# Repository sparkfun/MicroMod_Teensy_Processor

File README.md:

SparkFun MicroMod Teensy Processor Board 
========================================

[SparkFun MicroMod Teensy Processor Board](https://www.sparkfun.com/products/16402)

The SparkFun MicroMod Teensy Processor Board leverages the incredible computing power of the NXP iMXRT1062 chip and pairs it with the M.2 MicroMod connector to allow you to plug it into your choice of compatible SparkFun MicroMod Carrier Board.

Repository Contents
-------------------

* **/Documents** - Datasheets, schematic, etc.
* **/Hardware** - Eagle design files (.brd, .sch)

Documentation
--------------
* **[Hookup Guide](https://learn.sparkfun.com/tutorials/micromod-teensy-processor-hookup-guide)** - Basic hookup guide for the SparkFun MicroMod Teensy Processor Board
* **[MicroMod Info Page](https://www.sparkfun.com/micromod)** - MicroMod Information Page

Version History
---------------
* **[DEV-16402](https://www.sparkfun.com/products/16402)** - Initial release.

License Information
-------------------

This product is _**open source**_! 

Please review the LICENSE.md file for license information. 

If you have any questions or concerns on licensing, please contact technical support on our [SparkFun forums](https://forum.sparkfun.com/viewforum.php?f=152).

Distributed as-is; no warranty is given.

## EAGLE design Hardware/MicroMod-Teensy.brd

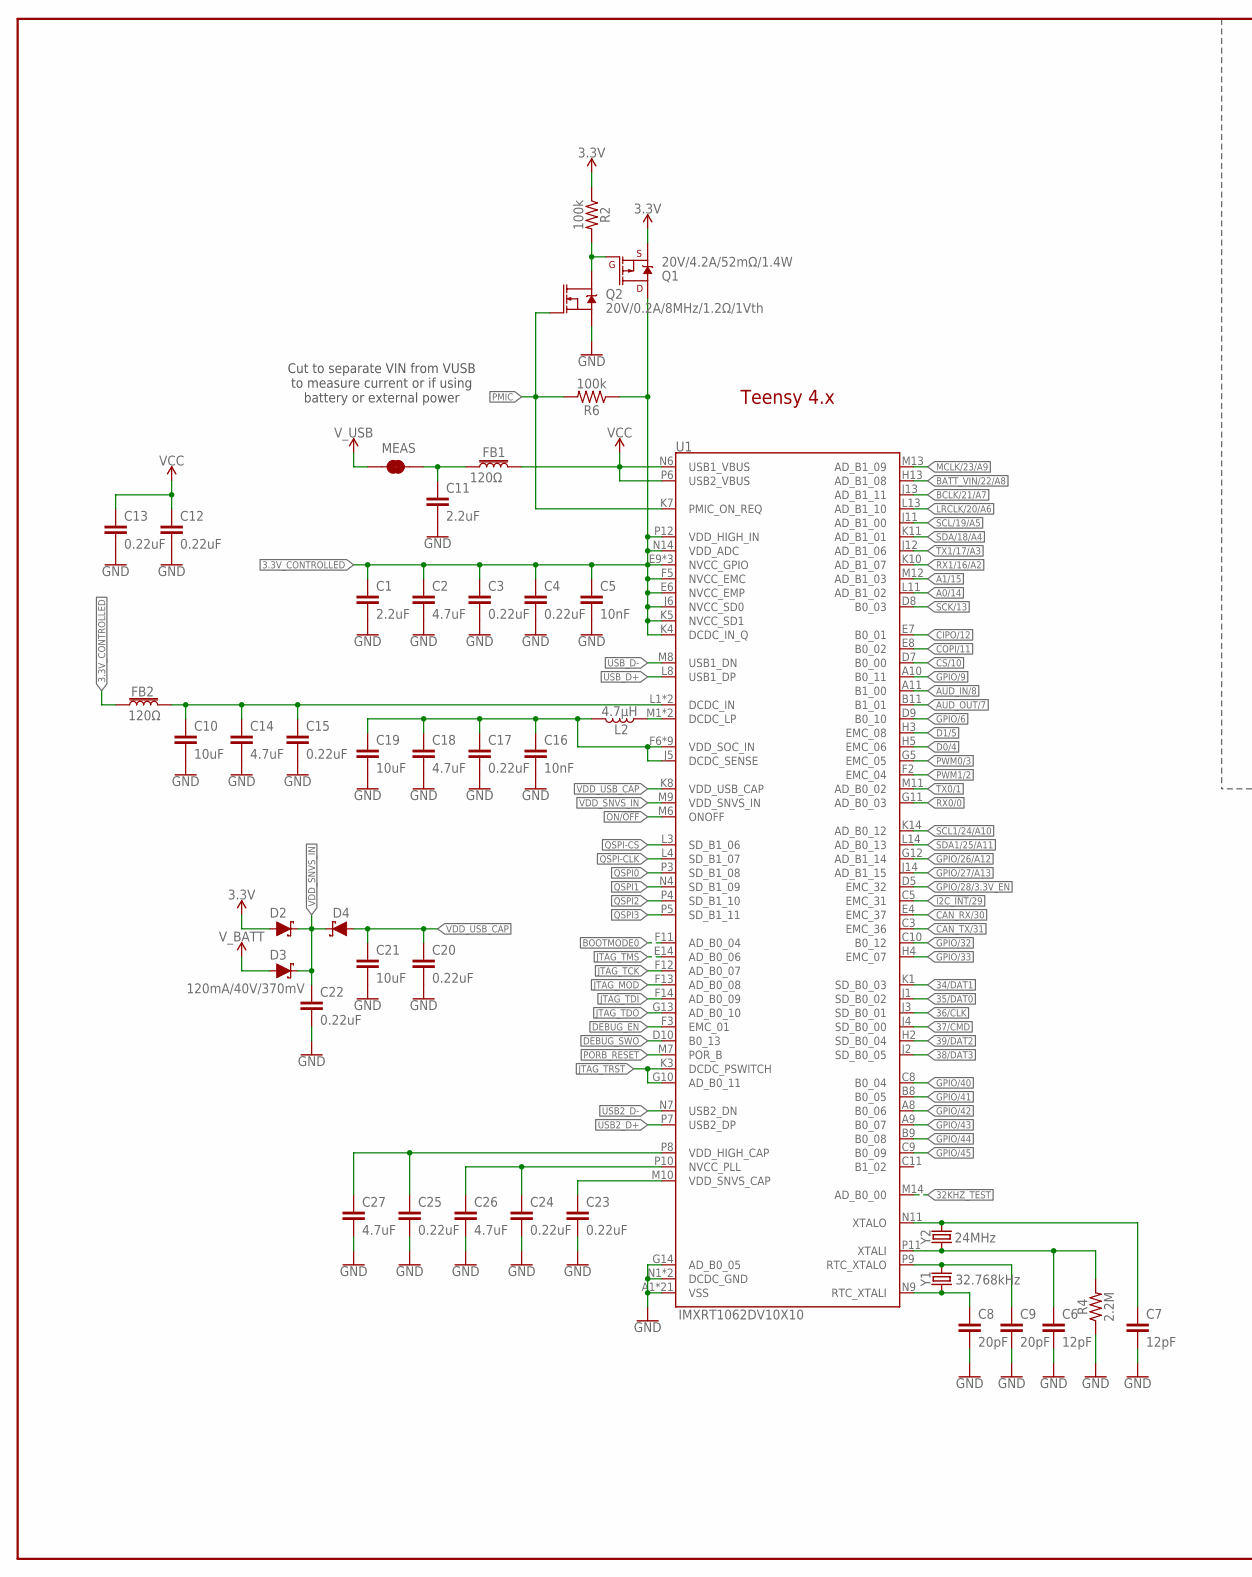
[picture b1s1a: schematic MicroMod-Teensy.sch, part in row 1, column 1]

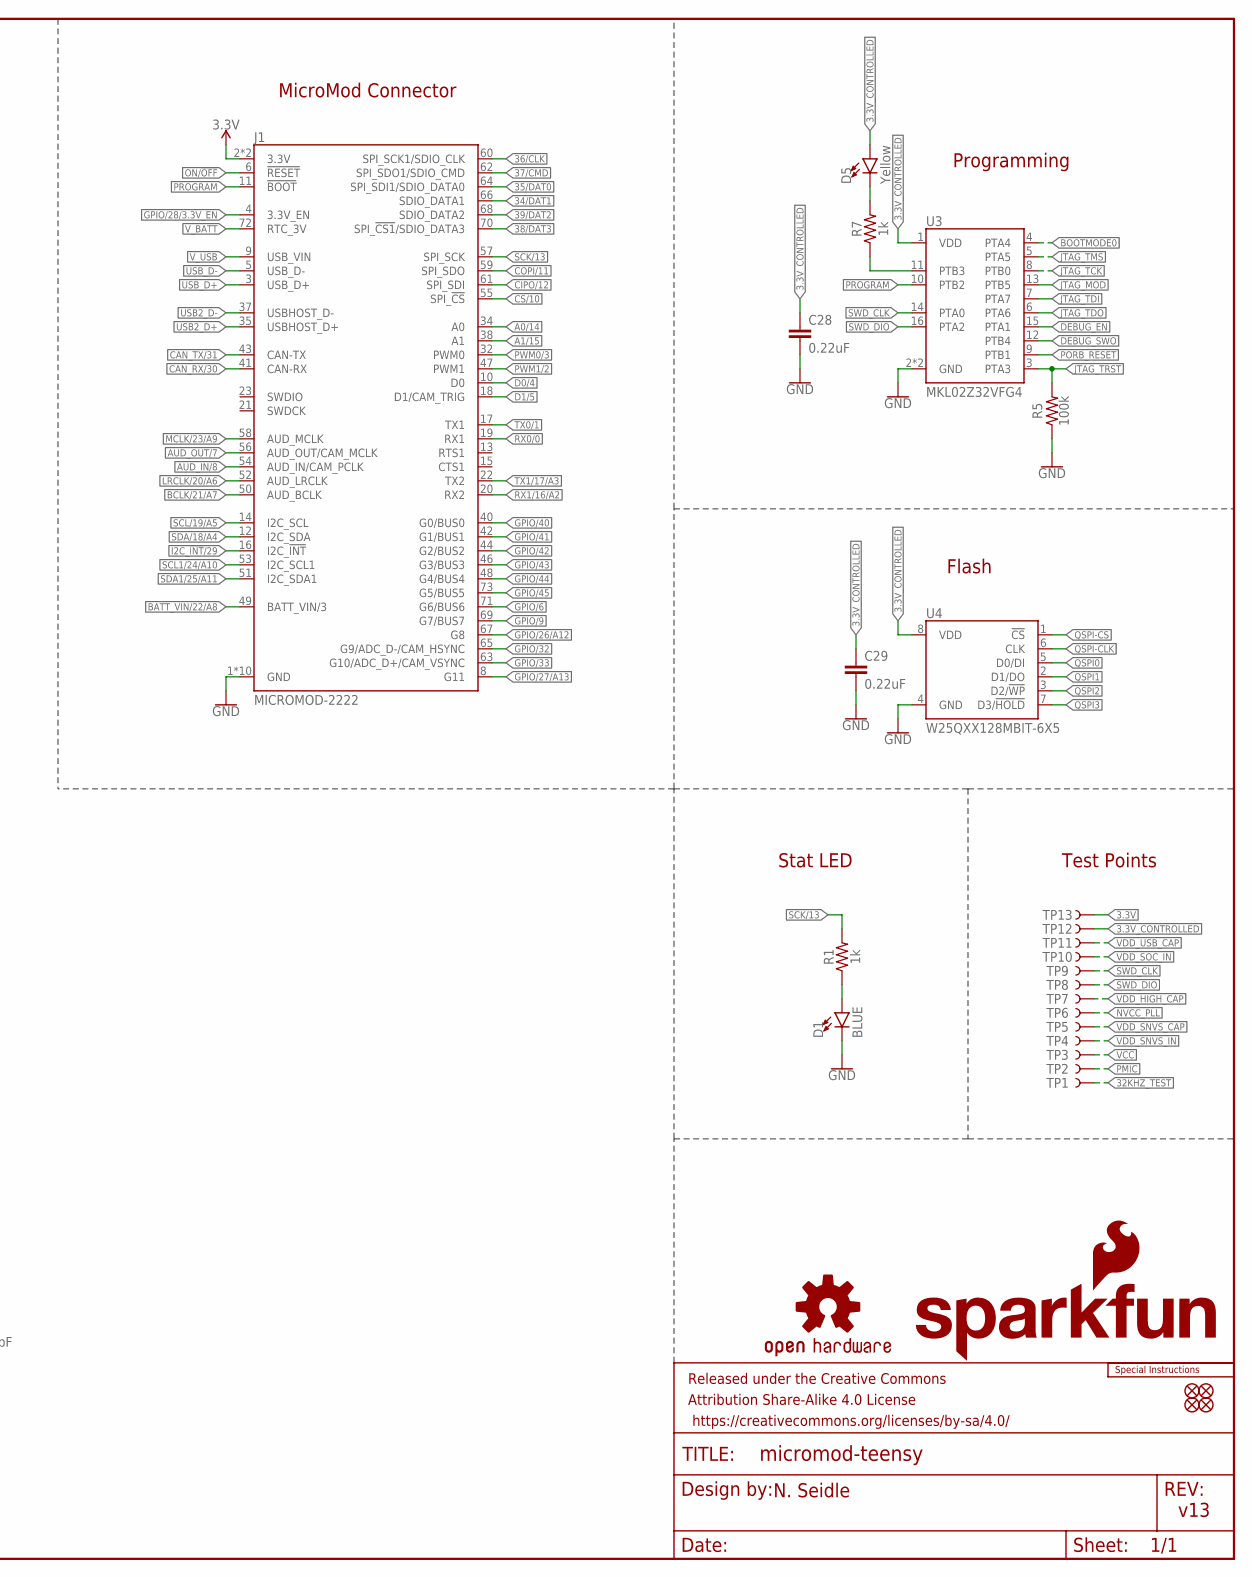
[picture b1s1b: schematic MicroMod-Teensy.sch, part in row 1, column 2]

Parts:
C1, C11: 2.2uF; 0402-TIGHT
C2, C14, C18, C26, C27: 4.7uF; 0402-TIGHT
C3, C4, C12, C13, C15, C17, C20, C22, C23, C24, C25, C28, C29: 0.22uF; 0402-TIGHT
C5, C16: 10nF; 0402-TIGHT
C6, C7: 12pF; 0402-TIGHT
C8, C9: 20pF; 0402-TIGHT
C10, C19, C21: 10uF; 0402-TIGHT
D1: BLUE; LED-0603
D2, D3, D4: 120mA/40V/370mV; SOD-523
D5: Yellow; LED-0603
FB1, FB2: 120Ω; 0402-TIGHT
FD1, FD2, FD3, FD4: FIDUCIALUFIDUCIAL; FIDUCIAL-MICRO
FRAME1: FRAME-LEDGER; CREATIVE_COMMONS
J1: MICROMOD-2222; M.2-CARD-E-22
L2: 4.7μH; 1008(2520)
LOGO1: SFE_LOGO_NAME_FLAME.1_INCH; SFE_LOGO_NAME_FLAME_.1
LOGO2: OSHW-LOGONO_SILK; DUMMY
LOGO3: SPECIAL_INSTRUCTIONS-ORDERING; ORDERING_INSTRUCTIONS
MEAS: JUMPER-SMT_2_NC_TRACE_SILK; SMT-JUMPER_2_NC_TRACE_SILK
Q1: 20V/4.2A/52mΩ/1.4W; SOT23-3
Q2: 20V/0.2A/8MHz/1.2Ω/1Vth; SOT-416FL
R1, R7: 1k; 0402-TIGHT
R2, R5, R6: 100k; 0402-TIGHT
R4: 2.2M; 0402-TIGHT
TP1, TP2, TP3, TP4, TP5, TP6, TP7, TP8, TP9, TP10, TP11, TP12, TP13: TEST-POINT3; PAD.03X.03
U1: IMXRT1062DV10X10; IMXRT1062
U3: MKL02Z32VFG4; QFN-16
U4: W25QXX128MBIT-6X5; WSON-8-6X5-SKINNY_CENTERPAD
Y1: 32.768kHz; CRYSTAL-SMD-3.2X1.5MM
Y2: 24MHz; CRYSTAL-SMD-2.0X1.6MM

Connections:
3.3V: D2.A, J1.2 (3.3V), J1.74 (3.3V), Q1.2 (S), R2.1, TP13.P$1
3.3V_CONTROLLED: C1.1, C2.1, C3.1, C4.1, C5.1, C28.1, C29.1, D5.A, FB2.1, Q1.3 (D), R6.1, TP12.P$1, U1.E6 (NVCC_EMP), U1.E9 (NVCC_GPIO), U1.F5 (NVCC_EMC), U1.F10 (NVCC_GPIO), U1.J6 (NVCC_SD0), U1.J10 (NVCC_GPIO), U1.K4 (DCDC_IN_Q), U1.K5 (NVCC_SD1), U1.N14 (VDD_ADC), U1.P12 (VDD_HIGH_IN), U3.1 (VDD), U4.8 (VDD)
24MHZ_1: C7.1, U1.N11 (XTALO), Y2.3 (2)
24MHZ_2: C6.1, R4.2, U1.P11 (XTALI), Y2.1
32KHZ_1: C8.1, U1.N9 (RTC_XTALI), Y1.P$1 (1)
32KHZ_2: C9.1, U1.P9 (RTC_XTALO), Y1.P$2 (2)
32KHZ_TEST: TP1.P$1, U1.M14 (AD_B0_00)
34/DAT1: J1.66 (SDIO_DATA1), U1.K1 (SD_B0_03)
35/DAT0: J1.64 (SPI_SDI1/SDIO_DATA0), U1.J1 (SD_B0_02)
36/CLK: J1.60 (SPI_SCK1/SDIO_CLK), U1.J3 (SD_B0_01)
37/CMD: J1.62 (SPI_SDO1/SDIO_CMD), U1.J4 (SD_B0_00)
38/DAT3: J1.70 (SPI_!CS1!/SDIO_DATA3), U1.J2 (SD_B0_05)
39/DAT2: J1.68 (SDIO_DATA2), U1.H2 (SD_B0_04)
A0/14: J1.34 (A0), U1.L11 (AD_B1_02)
A1/15: J1.38 (A1), U1.M12 (AD_B1_03)
AUD_IN/8: J1.54 (AUD_IN/CAM_PCLK), U1.A11 (B1_00)
AUD_OUT/7: J1.56 (AUD_OUT/CAM_MCLK), U1.B11 (B1_01)
BATT_VIN/22/A8: J1.49 (BATT_VIN/3), U1.H13 (AD_B1_08)
BCLK/21/A7: J1.50 (AUD_BCLK), U1.J13 (AD_B1_11)
BOOTMODE0: U1.F11 (AD_B0_04), U3.4 (PTA4)
CAN_RX/30: J1.41 (CAN-RX), U1.E4 (EMC_37)
CAN_TX/31: J1.43 (CAN-TX), U1.C3 (EMC_36)
CIPO/12: J1.61 (SPI_SDI), U1.E7 (B0_01)
COPI/11: J1.59 (SPI_SDO), U1.E8 (B0_02)
CS/10: J1.55 (SPI_!CS!), U1.D7 (B0_00)
D0/4: J1.10 (D0), U1.H5 (EMC_06)
D1/5: J1.18 (D1/CAM_TRIG), U1.H3 (EMC_08)
DCDC_IN: C10.1, C14.1, C15.1, FB2.2, U1.L1 (DCDC_IN), U1.L2 (DCDC_IN)
DCDC_LP: L2.1, U1.M1 (DCDC_LP), U1.M2 (DCDC_LP)
DEBUG_EN: U1.F3 (EMC_01), U3.15 (PTA1)
DEBUG_SWO: U1.D10 (B0_13), U3.12 (PTB4)
GND: C1.2, C2.2, C3.2, C4.2, C5.2, C6.2, C7.2, C8.2, C9.2, C10.2, C11.2, C12.2, C13.2, C14.2, C15.2, C16.2, C17.2, C18.2, C19.2, C20.2, C21.2, C22.2, C23.2, C24.2, C25.2, C26.2, C27.2, C28.2, C29.2, D1.C, J1.1 (GND), J1.7 (GND), J1.33 (GND), J1.36 (GND), J1.39 (GND), J1.45 (GND), J1.75 (GND), J1.GND1 (GND), J1.GND2 (GND), J1.GND3 (GND), Q2.2 (S), R4.1, R5.1, U1.A1 (VSS), U1.A14 (VSS), U1.B5 (VSS), U1.B10 (VSS), U1.E2 (VSS), U1.E13 (VSS), U1.G7 (VSS), U1.G8 (VSS), U1.G14 (AD_B0_05), U1.H7 (VSS), U1.H8 (VSS), U1.J7 (VSS), U1.J8 (VSS), U1.K2 (VSS), U1.K6 (VSS), U1.K9 (VSS), U1.K13 (VSS), U1.L9 (VSS), U1.N1 (DCDC_GND), U1.N2 (DCDC_GND), U1.N5 (VSS), U1.N8 (VSS), U1.P1 (VSS), U1.P14 (VSS), U3.2 (GND), U3.17 (GND), U4.4 (GND)
GPIO/6: J1.71 (G6/BUS6), U1.D9 (B0_10)
GPIO/9: J1.69 (G7/BUS7), U1.A10 (B0_11)
GPIO/26/A12: J1.67 (G8), U1.G12 (AD_B1_14)
GPIO/27/A13: J1.8 (G11), U1.J14 (AD_B1_15)
GPIO/28/3.3V_EN: J1.4 (3.3V_EN), U1.D5 (EMC_32)
GPIO/32: J1.65 (G9/ADC_D-/CAM_HSYNC), U1.C10 (B0_12)
GPIO/33: J1.63 (G10/ADC_D+/CAM_VSYNC), U1.H4 (EMC_07)
GPIO/40: J1.40 (G0/BUS0), U1.C8 (B0_04)
GPIO/41: J1.42 (G1/BUS1), U1.B8 (B0_05)
GPIO/42: J1.44 (G2/BUS2), U1.A8 (B0_06)
GPIO/43: J1.46 (G3/BUS3), U1.A9 (B0_07)
GPIO/44: J1.48 (G4/BUS4), U1.B9 (B0_08)
GPIO/45: J1.73 (G5/BUS5), U1.C9 (B0_09)
I2C_!INT!/29: J1.16 (I2C_!INT!), U1.C5 (EMC_31)
JTAG_MOD: U1.F13 (AD_B0_08), U3.13 (PTB5)
JTAG_TCK: U1.F12 (AD_B0_07), U3.8 (PTB0)
JTAG_TDI: U1.F14 (AD_B0_09), U3.7 (PTA7)
JTAG_TDO: U1.G13 (AD_B0_10), U3.6 (PTA6)
JTAG_TMS: U1.E14 (AD_B0_06), U3.5 (PTA5)
JTAG_TRST: R5.2, U1.G10 (AD_B0_11), U1.K3 (DCDC_PSWITCH), U3.3 (PTA3)
LRCLK/20/A6: J1.52 (AUD_LRCLK), U1.L13 (AD_B1_10)
MCLK/23/A9: J1.58 (AUD_MCLK), U1.M13 (AD_B1_09)
unnamed: D1.A, R1.1
unnamed: Q1.1 (G), Q2.3 (D), R2.2
unnamed: C11.1, FB1.1, MEAS.2
unnamed: R7.1, U3.11 (PTB3)
unnamed: D5.C, R7.2
NVCC_PLL: C24.1, C26.1, TP6.P$1, U1.P10 (NVCC_PLL)
ON/!OFF!: J1.6 (!RESET!), U1.M6 (ONOFF)
PMIC: Q2.1 (G), R6.2, TP2.P$1, U1.K7 (PMIC_ON_REQ)
PORB_RESET: U1.M7 (POR_B), U3.9 (PTB1)
PROGRAM: J1.11 (!BOOT!), U3.10 (PTB2)
PWM0/3: J1.32 (PWM0), U1.G5 (EMC_05)
PWM1/2: J1.47 (PWM1), U1.F2 (EMC_04)
QSPI0: U1.P3 (SD_B1_08), U4.5 (D0/DI)
QSPI1: U1.N4 (SD_B1_09), U4.2 (D1/DO)
QSPI2: U1.P4 (SD_B1_10), U4.3 (D2/!WP!)
QSPI3: U1.P5 (SD_B1_11), U4.7 (D3/!HOLD!)
QSPI-CLK: U1.L4 (SD_B1_07), U4.6 (CLK)
QSPI-CS: U1.L3 (SD_B1_06), U4.1 (!CS!)
RX0/0: J1.19 (RX1), U1.G11 (AD_B0_03)
RX1/16/A2: J1.20 (RX2), U1.K10 (AD_B1_07)
SCK/13: J1.57 (SPI_SCK), R1.2, U1.D8 (B0_03)
SCL1/24/A10: J1.53 (I2C_SCL1), U1.K14 (AD_B0_12)
SCL/19/A5: J1.14 (I2C_SCL), U1.J11 (AD_B1_00)
SDA1/25/A11: J1.51 (I2C_SDA1), U1.L14 (AD_B0_13)
SDA/18/A4: J1.12 (I2C_SDA), U1.K11 (AD_B1_01)
SWD_CLK: TP9.P$1, U3.14 (PTA0)
SWD_DIO: TP8.P$1, U3.16 (PTA2)
TX0/1: J1.17 (TX1), U1.M11 (AD_B0_02)
TX1/17/A3: J1.22 (TX2), U1.J12 (AD_B1_06)
USB2_D+: J1.35 (USBHOST_D+), U1.P7 (USB2_DP)
USB2_D-: J1.37 (USBHOST_D-), U1.N7 (USB2_DN)
USB_D+: J1.3 (USB_D+), U1.L8 (USB1_DP)
USB_D-: J1.5 (USB_D-), U1.M8 (USB1_DN)
VCC: C12.1, C13.1, FB1.2, TP3.P$1, U1.N6 (USB1_VBUS), U1.P6 (USB2_VBUS)
VDD_HIGH_CAP: C25.1, C27.1, TP7.P$1, U1.P8 (VDD_HIGH_CAP)
VDD_SNVS_CAP: C23.1, TP5.P$1, U1.M10 (VDD_SNVS_CAP)
VDD_SNVS_IN: C22.1, D2.C, D3.C, D4.C, TP4.P$1, U1.M9 (VDD_SNVS_IN)
VDD_SOC_IN: C16.1, C17.1, C18.1, C19.1, L2.2, TP10.P$1, U1.F6 (VDD_SOC_IN), U1.F7 (VDD_SOC_IN), U1.F8 (VDD_SOC_IN), U1.F9 (VDD_SOC_IN), U1.G6 (VDD_SOC_IN), U1.G9 (VDD_SOC_IN), U1.H6 (VDD_SOC_IN), U1.H9 (VDD_SOC_IN), U1.J5 (DCDC_SENSE), U1.J9 (VDD_SOC_IN)
VDD_USB_CAP: C20.1, C21.1, D4.A, TP11.P$1, U1.K8 (VDD_USB_CAP)
V_BATT: D3.A, J1.72 (RTC_3V)
V_USB: J1.9 (USB_VIN), MEAS.1

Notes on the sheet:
v13
N. Seidle
MicroMod Connector
Teensy 4.x
Flash
Stat LED
Programming
Cut to separate VIN from VUSB to measure current or if using battery or external power
Test Points

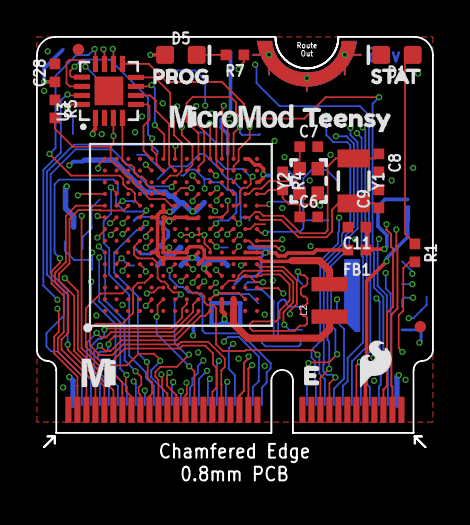
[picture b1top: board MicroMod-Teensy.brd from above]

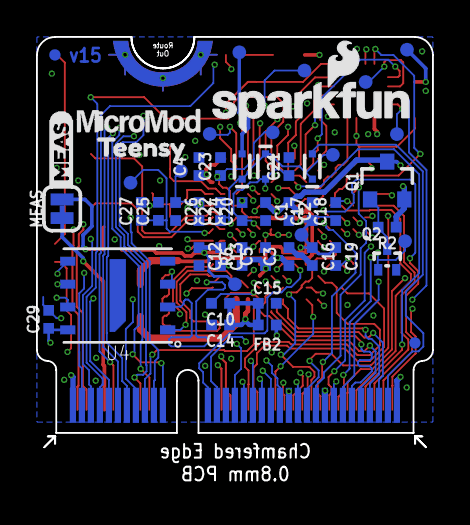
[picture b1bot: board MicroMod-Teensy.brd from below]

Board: 4 copper layers, 22.0 x 22.8 mm, 82 parts (52 on the bottom side), 95 nets.

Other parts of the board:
U$1, U$3: TEENSY2
U$4: MICROMOD_MI_LOGO_.35
U$6: SFE_LOGO_FLAME_.1
U$7, U$11: MICROMOD_LOGO_.3
U$8: MEAS2
U$9: PROG0
U$10: STAT1

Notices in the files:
parts and their libraries:
SparkFun-Aesthetics: Licensing: Creative Commons ShareAlike 4.0 International - https://creativecommons.org/licenses/by-sa/4.0
SparkFun-Aesthetics: Released under the Creative Commons Attribution Share-Alike 4.0 License
SparkFun-Aesthetics: https://creativecommons.org/licenses/by-sa/4.0
